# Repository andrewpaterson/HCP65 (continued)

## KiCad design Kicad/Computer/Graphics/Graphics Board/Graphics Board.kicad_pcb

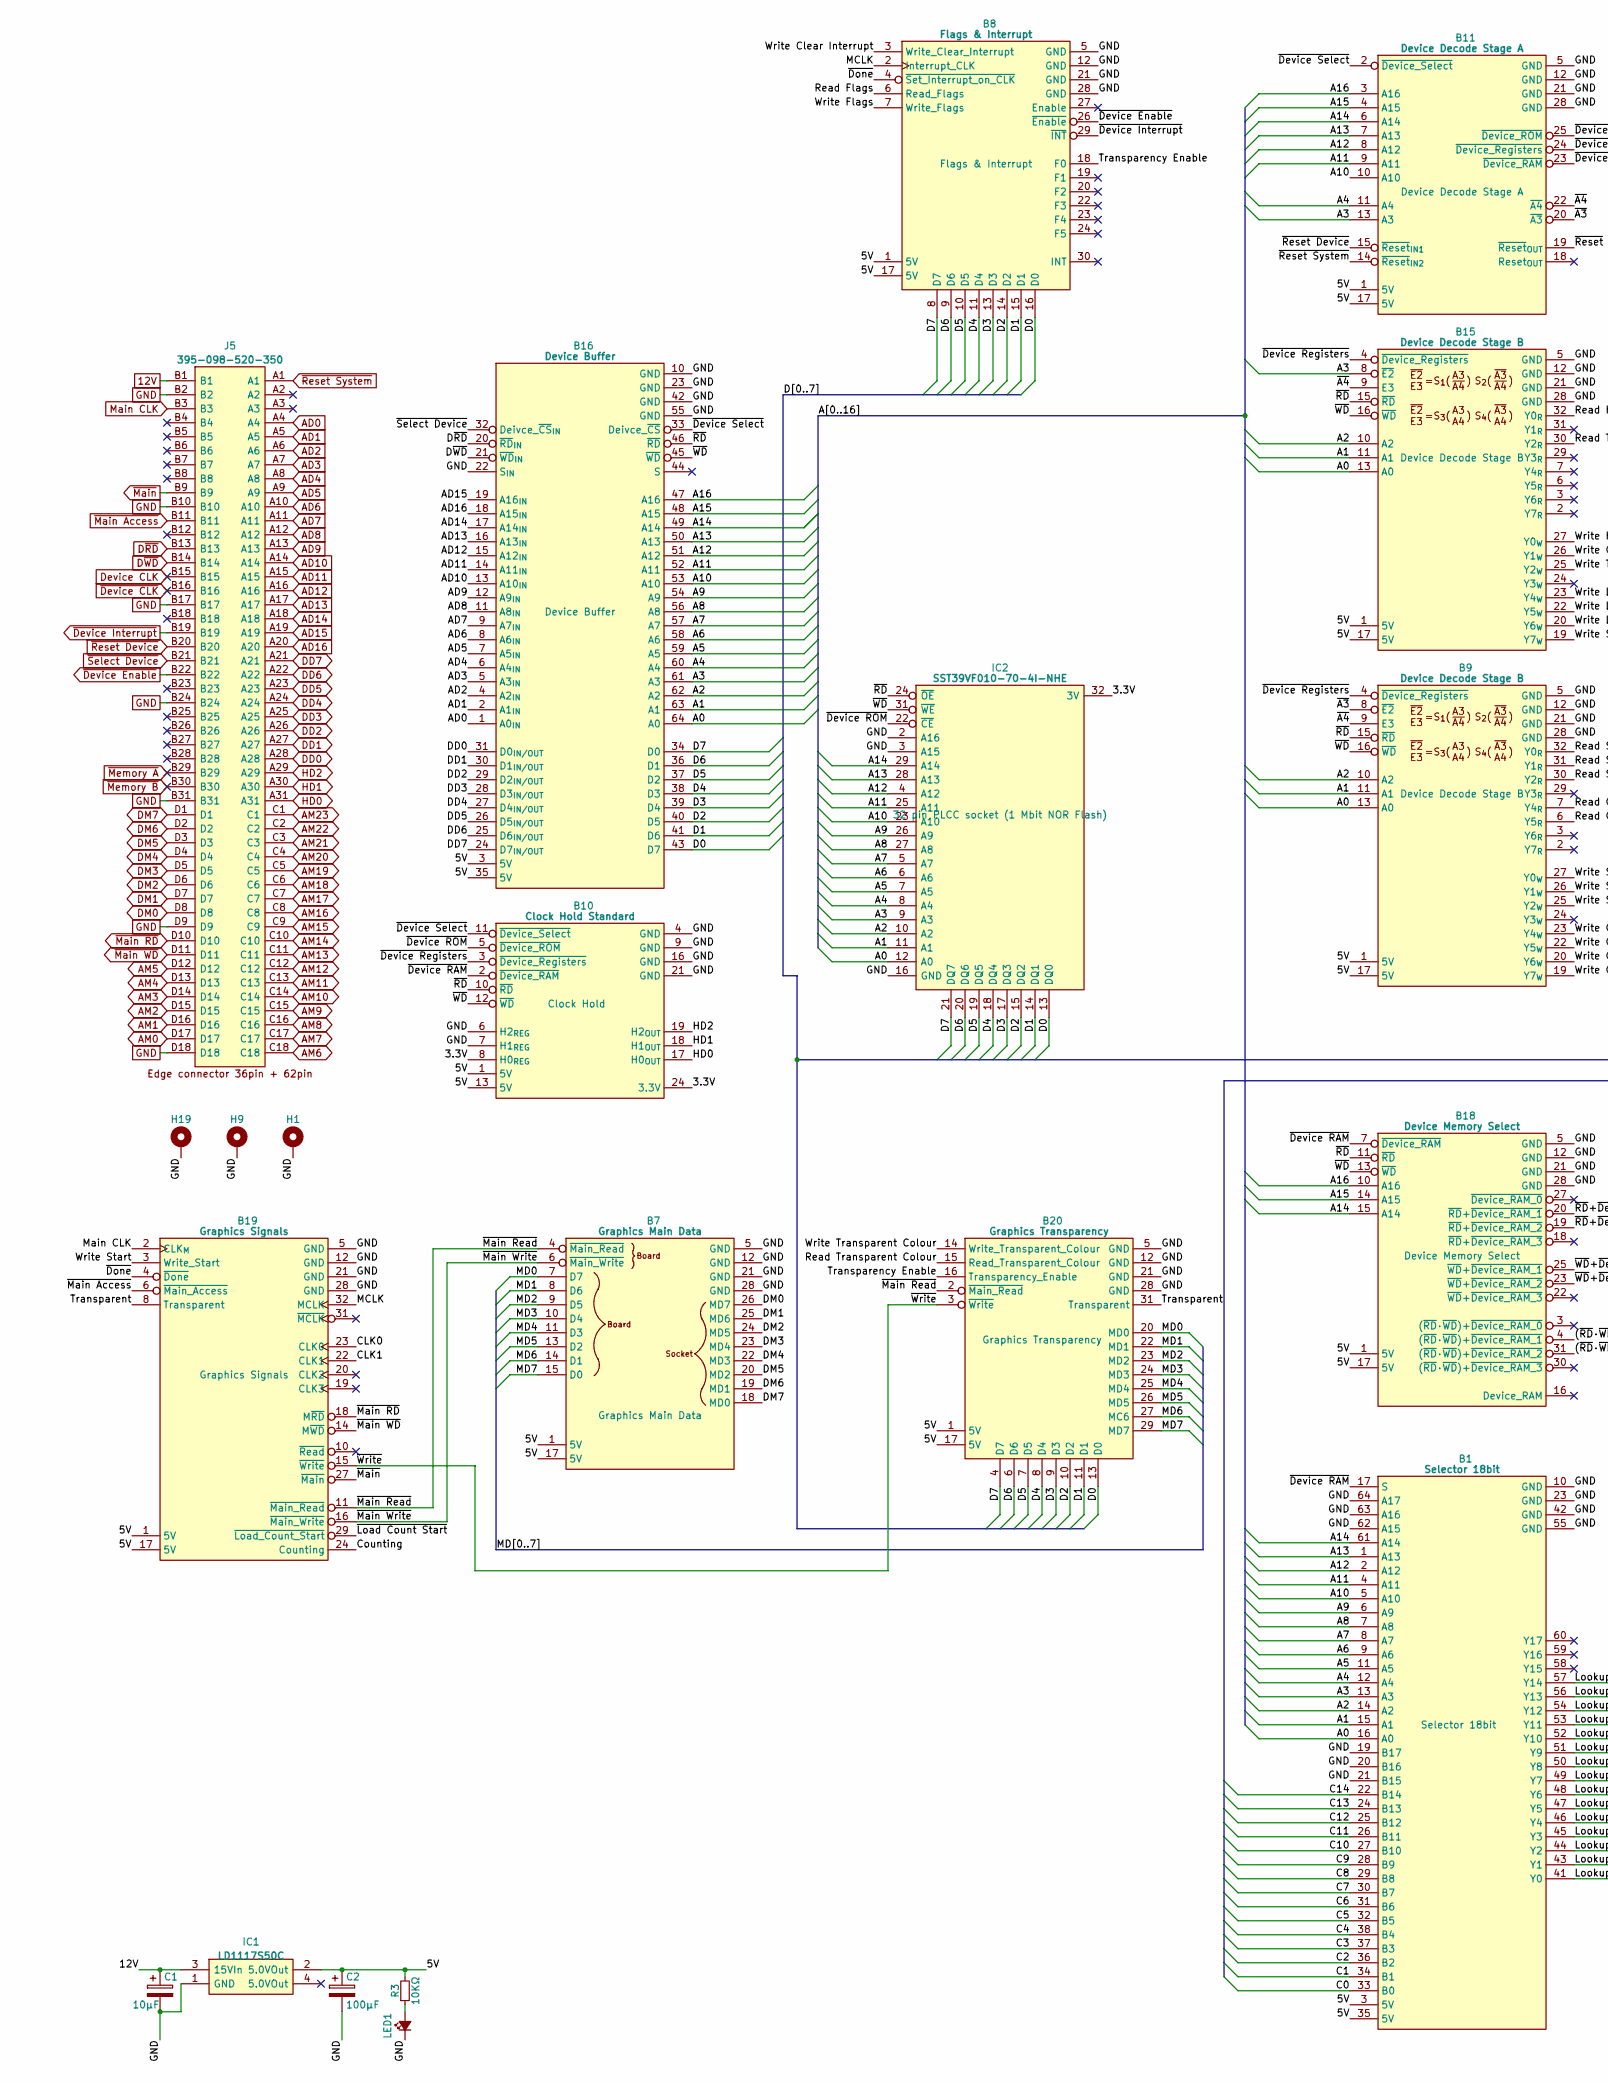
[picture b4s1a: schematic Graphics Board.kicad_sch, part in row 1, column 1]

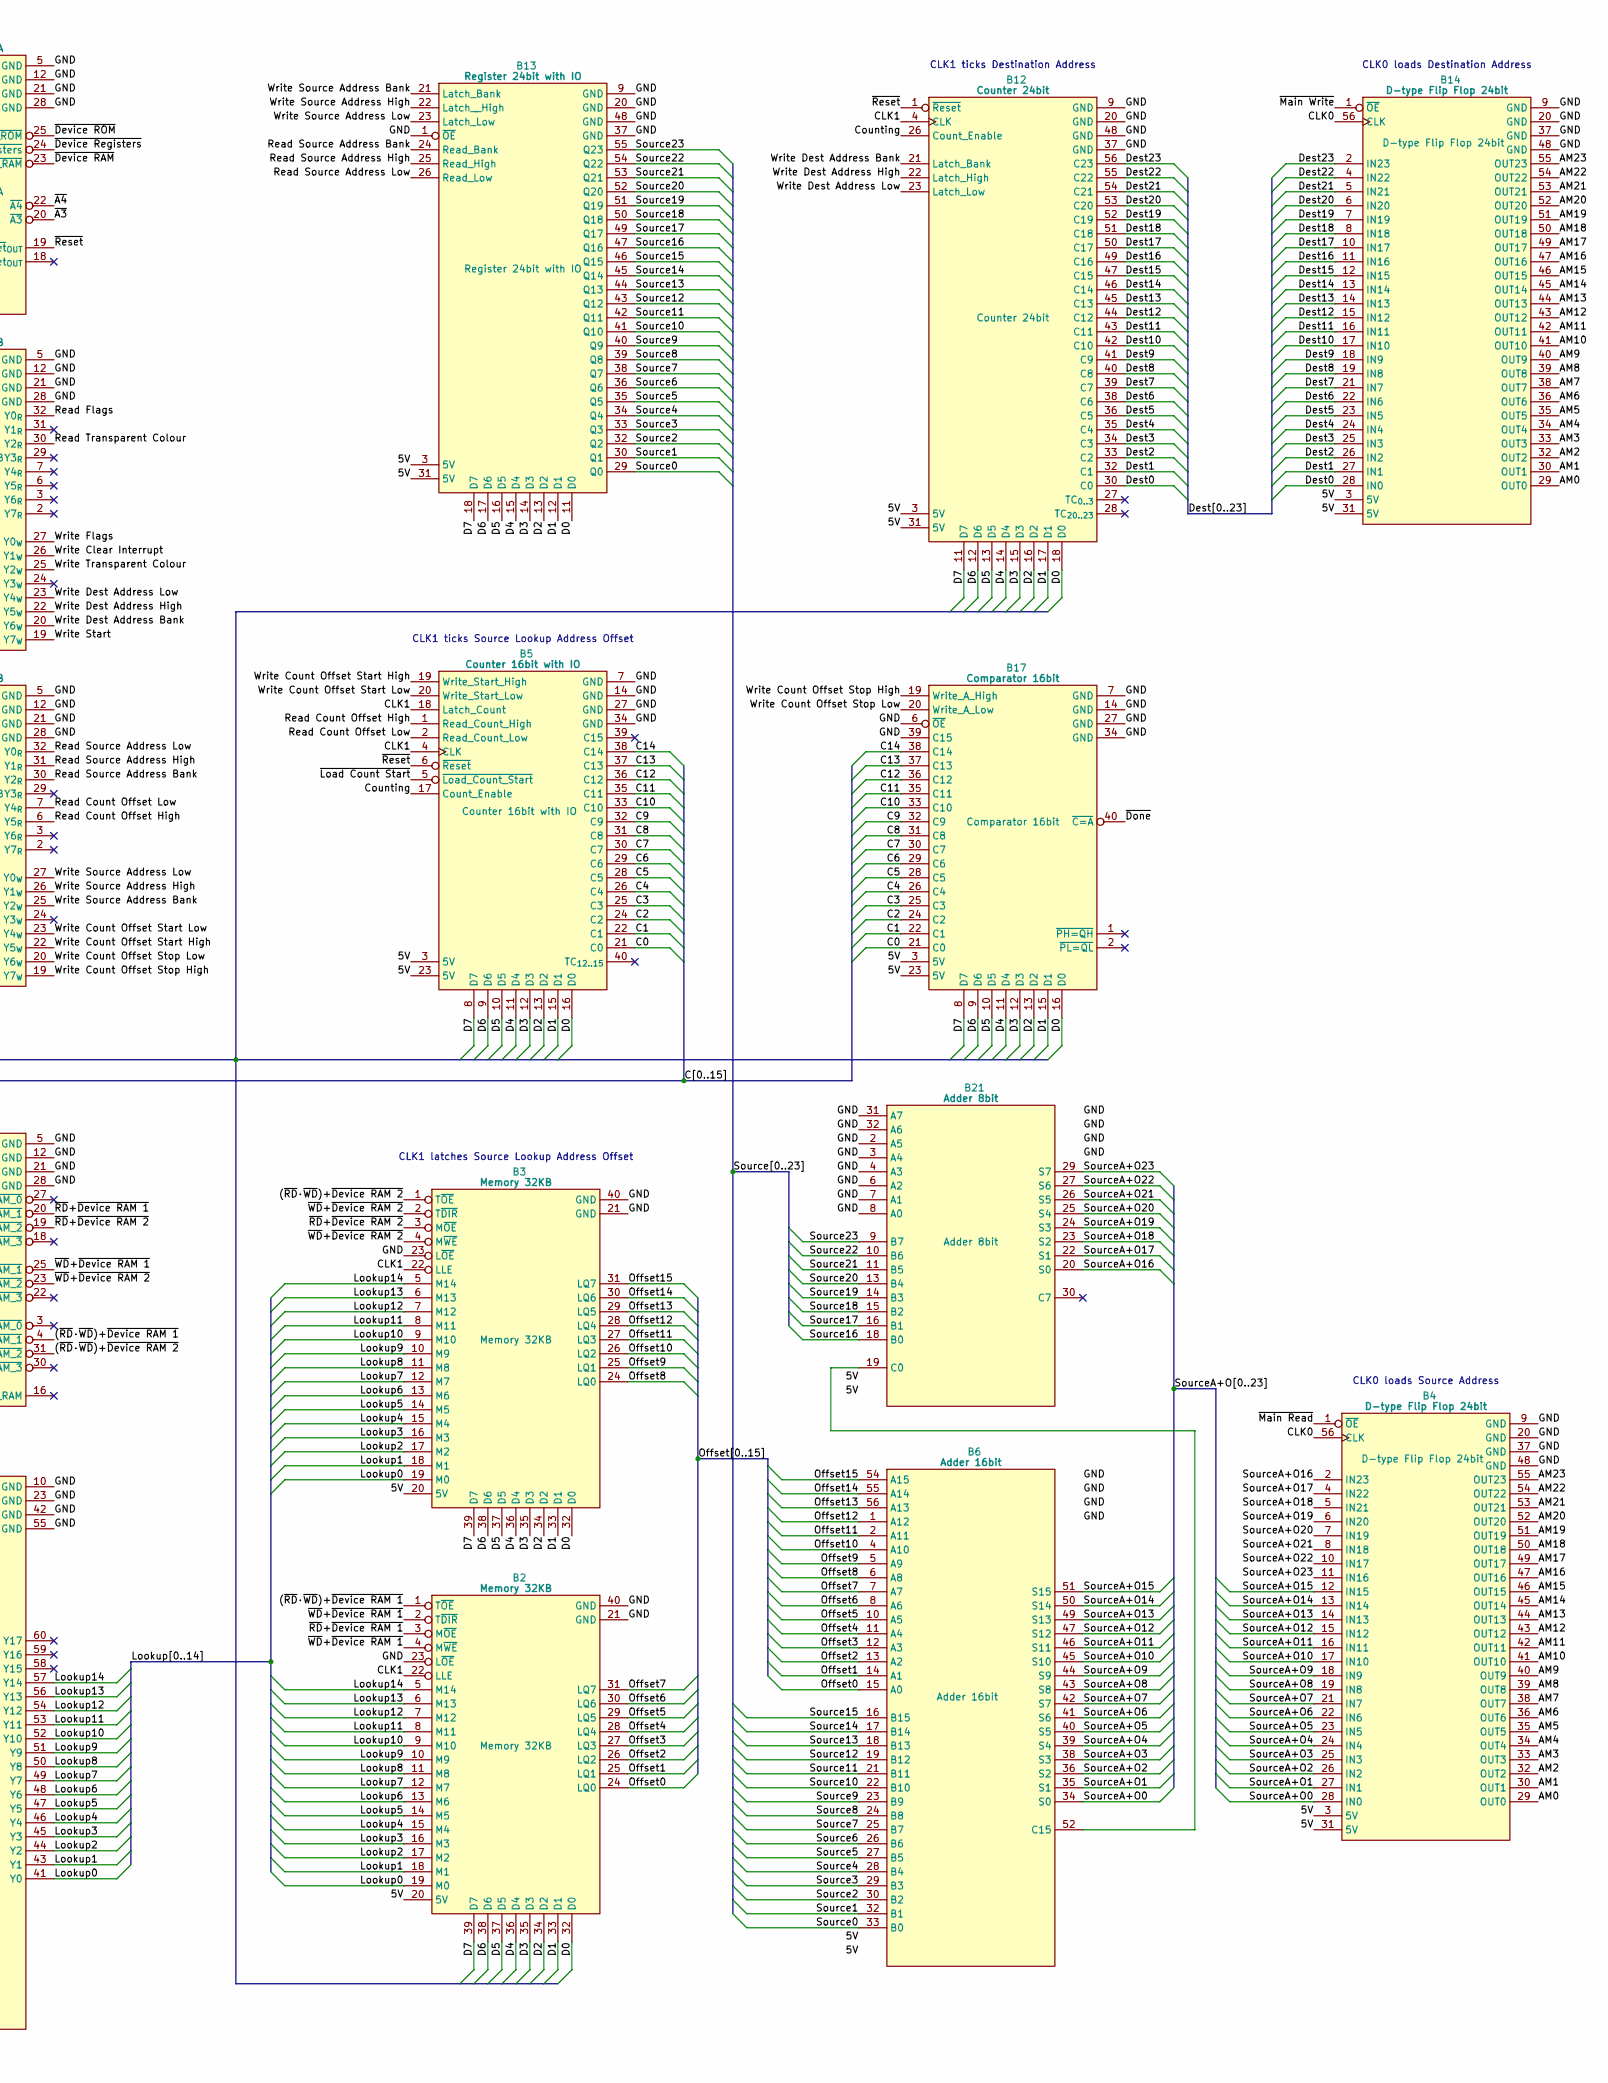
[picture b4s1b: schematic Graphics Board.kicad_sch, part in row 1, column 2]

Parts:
B1: Selector 18bit; HCP65_Selector_18bit
B2, B3: Memory 32KB; HCP65_Memory_32KB_With_Latch
B4, B14: D-type Flip Flop 24bit; HCP65_D_Flip_Flop_24bit
B5: Counter 16bit with IO; HCP65_Counter_16bit_DIO
B6: Adder 16bit; HCP65_Adder_16bit
B7: Graphics Main Data; HCP65_Graphics_Main_Data
B8: Flags & Interrupt; HCP65_Flags_Interrupt
B9, B15: Device Decode Stage B; HCP65_Device_Decode_Stage_B
B10: Clock Hold Standard; HCP65_Clock_Hold_Standard
B11: Device Decode Stage A; HCP65_Device_Decode_Stage_A
B12: Counter 24bit; HCP65_Counter_24bit
B13: Register 24bit with IO; HCP65_Register_24bit_DIO
B16: Device Buffer; HCP65_Device_Buffer
B17: Comparator 16bit; HCP65_Comparator_16bit
B18: Device Memory Select; HCP65_Video_Device_RAM_Select
B19: Graphics Signals; HCP65_Graphics_Signals
B20: Graphics Transparency; HCP65_Graphics_Transparency
B21: Adder 8bit; HCP65_Adder_8bit
C1: 10μF; CP_Radial_D4.0mm_P2.00mm
C2: 100μF; CP_Radial_D4.0mm_P2.00mm
H1, H9, H19: MountingHole_Pad; HCP65_MountingHole_M3_
IC1: LD1117S50C; LD1117S33C; Manufacturer_Part_Number LD1117S50C
IC2: SST39VF010-70-4I-NHE; 5408803224008; Manufacturer_Part_Number SST39VF010-70-4I-NHE
J5: 395-098-520-350; 98pin Edge Connector; Manufacturer_Part_Number 395-098-520-350; Mouser Part Number 587-395-098-520-350
LED1: LED; LED_D5.0mm
R3: 10KΩ; R_0805

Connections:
12V: C1.1, IC1.3 (15VIn), J5.B1
/3.3V: B10.8 (H0_{REG}), B10.24 (3.3V), IC2.32 (3V)
/5V: B1.3 (5V), B1.35 (5V), B2.20 (5V), B3.20 (5V), B4.3 (5V), B4.31 (5V), B5.3 (5V), B5.23 (5V), B6.3 (5V), B6.31 (5V), B7.1 (5V), B7.17 (5V), B8.1 (5V), B8.17 (5V), B9.1 (5V), B9.17 (5V), B10.1 (5V), B10.13 (5V), B11.1 (5V), B11.17 (5V), B12.3 (5V), B12.31 (5V), B13.3 (5V), B13.31 (5V), B14.3 (5V), B14.31 (5V), B15.1 (5V), B15.17 (5V), B16.3 (5V), B16.35 (5V), B17.3 (5V), B17.23 (5V), B18.1 (5V), B18.17 (5V), B19.1 (5V), B19.17 (5V), B20.1 (5V), B20.17 (5V), B21.1 (5V), B21.17 (5V), C2.1, IC1.2 (5.0VOut), R3.2
/(~RD·~WD)+~Device RAM 1: B2.1 (T~OE), B18.4 ((~RD·~WD)+~Device_RAM_1)
/(~RD·~WD)+~Device RAM 2: B3.1 (T~OE), B18.31 ((~RD·~WD)+~Device_RAM_2)
/A0: B1.16 (A0), B9.13 (A0), B15.13 (A0), B16.64 (A0), IC2.12 (A0)
/A1: B1.15 (A1), B9.11 (A1), B15.11 (A1), B16.63 (A1), IC2.11 (A1)
/A2: B1.14 (A2), B9.10 (A2), B15.10 (A2), B16.62 (A2), IC2.10 (A2)
/A3: B1.13 (A3), B11.13 (A3), B15.8 (~E2), B16.61 (A3), IC2.9 (A3)
/A4: B1.12 (A4), B11.11 (A4), B16.60 (A4), IC2.8 (A4)
/A5: B1.11 (A5), B16.59 (A5), IC2.7 (A5)
/A6: B1.9 (A6), B16.58 (A6), IC2.6 (A6)
/A7: B1.8 (A7), B16.57 (A7), IC2.5 (A7)
/A8: B1.7 (A8), B16.56 (A8), IC2.27 (A8)
/A9: B1.6 (A9), B16.54 (A9), IC2.26 (A9)
/A10: B1.5 (A10), B11.10 (A10), B16.53 (A10), IC2.23 (A10)
/A11: B1.4 (A11), B11.9 (A11), B16.52 (A11), IC2.25 (A11)
/A12: B1.2 (A12), B11.8 (A12), B16.51 (A12), IC2.4 (A12)
/A13: B1.1 (A13), B11.7 (A13), B16.50 (A13), IC2.28 (A13)
/A14: B1.61 (A14), B11.6 (A14), B16.49 (A14), B18.15 (A14), IC2.29 (A14)
/A15: B11.4 (A15), B16.48 (A15), B18.14 (A15)
/A16: B11.3 (A16), B16.47 (A16), B18.10 (A16)
/C0: B1.33 (B0), B5.21 (C0), B17.21 (C0)
/C1: B1.34 (B1), B5.22 (C1), B17.22 (C1)
/C2: B1.36 (B2), B5.24 (C2), B17.24 (C2)
/C3: B1.37 (B3), B5.25 (C3), B17.25 (C3)
/C4: B1.38 (B4), B5.26 (C4), B17.26 (C4)
/C5: B1.32 (B5), B5.28 (C5), B17.28 (C5)
/C6: B1.31 (B6), B5.29 (C6), B17.29 (C6)
/C7: B1.30 (B7), B5.30 (C7), B17.30 (C7)
/C8: B1.29 (B8), B5.31 (C8), B17.31 (C8)
/C9: B1.28 (B9), B5.32 (C9), B17.32 (C9)
/C10: B1.27 (B10), B5.33 (C10), B17.33 (C10)
/C11: B1.26 (B11), B5.35 (C11), B17.35 (C11)
/C12: B1.25 (B12), B5.36 (C12), B17.36 (C12)
/C13: B1.24 (B13), B5.37 (C13), B17.37 (C13)
/C14: B1.22 (B14), B5.38 (C14), B17.38 (C14)
/CLK0: B4.56 (CLK), B14.56 (CLK), B19.23 (CLK0)
/CLK1: B2.22 (LLE), B3.22 (LLE), B5.4 (CLK), B5.18 (Latch_Count), B12.4 (CLK), B19.22 (CLK1)
/Counting: B5.17 (Count_Enable), B12.26 (Count_Enable), B19.24 (Counting)
/D0: B2.32 (D0), B3.32 (D0), B5.16 (D0), B8.16 (D0), B12.18 (D0), B13.11 (D0), B16.43 (D7), B17.16 (D0), B20.13 (D0), IC2.13 (DQ0)
/D1: B2.33 (D1), B3.33 (D1), B5.15 (D1), B8.15 (D1), B12.17 (D1), B13.12 (D1), B16.41 (D6), B17.15 (D1), B20.11 (D1), IC2.14 (DQ1)
/D2: B2.34 (D2), B3.34 (D2), B5.13 (D2), B8.14 (D2), B12.16 (D2), B13.13 (D2), B16.40 (D5), B17.13 (D2), B20.10 (D2), IC2.15 (DQ2)
/D3: B2.35 (D3), B3.35 (D3), B5.12 (D3), B8.13 (D3), B12.15 (D3), B13.14 (D3), B16.39 (D4), B17.12 (D3), B20.9 (D3), IC2.17 (DQ3)
/D4: B2.36 (D4), B3.36 (D4), B5.11 (D4), B8.11 (D4), B12.14 (D4), B13.15 (D4), B16.38 (D3), B17.11 (D4), B20.8 (D4), IC2.18 (DQ4)
/D5: B2.37 (D5), B3.37 (D5), B5.10 (D5), B8.10 (D5), B12.13 (D5), B13.16 (D5), B16.37 (D2), B17.10 (D5), B20.7 (D5), IC2.19 (DQ5)
/D6: B2.38 (D6), B3.38 (D6), B5.9 (D6), B8.9 (D6), B12.12 (D6), B13.17 (D6), B16.36 (D1), B17.9 (D6), B20.6 (D6), IC2.20 (DQ6)
/D7: B2.39 (D7), B3.39 (D7), B5.8 (D7), B8.8 (D7), B12.11 (D7), B13.18 (D7), B16.34 (D0), B17.8 (D7), B20.4 (D7), IC2.21 (DQ7)
/Dest0: B12.30 (C0), B14.28 (IN0)
/Dest1: B12.32 (C1), B14.27 (IN1)
/Dest2: B12.33 (C2), B14.26 (IN2)
/Dest3: B12.34 (C3), B14.25 (IN3)
/Dest4: B12.35 (C4), B14.24 (IN4)
/Dest5: B12.36 (C5), B14.23 (IN5)
/Dest6: B12.38 (C6), B14.22 (IN6)
/Dest7: B12.39 (C7), B14.21 (IN7)
/Dest8: B12.40 (C8), B14.19 (IN8)
/Dest9: B12.41 (C9), B14.18 (IN9)
/Dest10: B12.42 (C10), B14.17 (IN10)
/Dest11: B12.43 (C11), B14.16 (IN11)
/Dest12: B12.44 (C12), B14.15 (IN12)
/Dest13: B12.45 (C13), B14.14 (IN13)
/Dest14: B12.46 (C14), B14.13 (IN14)
/Dest15: B12.47 (C15), B14.12 (IN15)
/Dest16: B12.49 (C16), B14.11 (IN16)
/Dest17: B12.50 (C17), B14.10 (IN17)
/Dest18: B12.51 (C18), B14.8 (IN18)
/Dest19: B12.52 (C19), B14.7 (IN19)
/Dest20: B12.53 (C20), B14.6 (IN20)
/Dest21: B12.54 (C21), B14.5 (IN21)
/Dest22: B12.55 (C22), B14.4 (IN22)
/Dest23: B12.56 (C23), B14.2 (IN23)
/Lookup0: B1.41 (Y0), B2.19 (M0), B3.19 (M0)
/Lookup1: B1.43 (Y1), B2.18 (M1), B3.18 (M1)
/Lookup2: B1.44 (Y2), B2.17 (M2), B3.17 (M2)
/Lookup3: B1.45 (Y3), B2.16 (M3), B3.16 (M3)
/Lookup4: B1.46 (Y4), B2.15 (M4), B3.15 (M4)
/Lookup5: B1.47 (Y5), B2.14 (M5), B3.14 (M5)
/Lookup6: B1.48 (Y6), B2.13 (M6), B3.13 (M6)
/Lookup7: B1.49 (Y7), B2.12 (M7), B3.12 (M7)
/Lookup8: B1.50 (Y8), B2.11 (M8), B3.11 (M8)
/Lookup9: B1.51 (Y9), B2.10 (M9), B3.10 (M9)
/Lookup10: B1.52 (Y10), B2.9 (M10), B3.9 (M10)
/Lookup11: B1.53 (Y11), B2.8 (M11), B3.8 (M11)
/Lookup12: B1.54 (Y12), B2.7 (M12), B3.7 (M12)
/Lookup13: B1.56 (Y13), B2.6 (M13), B3.6 (M13)
/Lookup14: B1.57 (Y14), B2.5 (M14), B3.5 (M14)
/MCLK: B8.2 (Interrupt_CLK), B19.32 (MCLK)
/MD0: B7.7 (D7), B20.20 (MD0)
/MD1: B7.8 (D6), B20.22 (MD1)
/MD2: B7.9 (D5), B20.23 (MD2)
/MD3: B7.10 (D4), B20.24 (MD3)
/MD4: B7.11 (D3), B20.25 (MD4)
/MD5: B7.13 (D2), B20.26 (MD5)
/MD6: B7.14 (D1), B20.27 (MC6)
/MD7: B7.15 (D0), B20.29 (MD7)
/Offset0: B2.24 (LQ0), B6.15 (A0)
/Offset1: B2.25 (LQ1), B6.14 (A1)
/Offset2: B2.26 (LQ2), B6.13 (A2)
/Offset3: B2.27 (LQ3), B6.12 (A3)
/Offset4: B2.28 (LQ4), B6.11 (A4)
/Offset5: B2.29 (LQ5), B6.10 (A5)
/Offset6: B2.30 (LQ6), B6.8 (A6)
/Offset7: B2.31 (LQ7), B6.7 (A7)
/Offset8: B3.24 (LQ0), B6.6 (A8)
/Offset9: B3.25 (LQ1), B6.5 (A9)
/Offset10: B3.26 (LQ2), B6.4 (A10)
/Offset11: B3.27 (LQ3), B6.2 (A11)
/Offset12: B3.28 (LQ4), B6.1 (A12)
/Offset13: B3.29 (LQ5), B6.56 (A13)
/Offset14: B3.30 (LQ6), B6.55 (A14)
/Offset15: B3.31 (LQ7), B6.54 (A15)
/Read Count Offset High: B5.1 (Read_Count_High), B9.6 (Y5_{R})
/Read Count Offset Low: B5.2 (Read_Count_Low), B9.7 (Y4_{R})
/Read Flags: B8.6 (Read_Flags), B15.32 (Y0_{R})
/Read Source Address Bank: B9.30 (Y2_{R}), B13.24 (Read_Bank)
/Read Source Address High: B9.31 (Y1_{R}), B13.25 (Read_High)
/Read Source Address Low: B9.32 (Y0_{R}), B13.26 (Read_Low)
/Read Transparent Colour: B15.30 (Y2_{R}), B20.15 (Read_Transparent_Colour)
/Source0: B6.33 (B0), B13.29 (Q0)
/Source1: B6.32 (B1), B13.30 (Q1)
/Source2: B6.30 (B2), B13.32 (Q2)
/Source3: B6.29 (B3), B13.33 (Q3)
/Source4: B6.28 (B4), B13.34 (Q4)
/Source5: B6.27 (B5), B13.35 (Q5)
/Source6: B6.26 (B6), B13.36 (Q6)
/Source7: B6.25 (B7), B13.38 (Q7)
/Source8: B6.24 (B8), B13.39 (Q8)
/Source9: B6.23 (B9), B13.40 (Q9)
/Source10: B6.22 (B10), B13.41 (Q10)
/Source11: B6.21 (B11), B13.42 (Q11)
/Source12: B6.19 (B12), B13.43 (Q12)
/Source13: B6.18 (B13), B13.44 (Q13)
/Source14: B6.17 (B14), B13.45 (Q14)
/Source15: B6.16 (B15), B13.46 (Q15)
/Source16: B13.47 (Q16), B21.18 (B0)
/Source17: B13.49 (Q17), B21.16 (B1)
/Source18: B13.50 (Q18), B21.15 (B2)
/Source19: B13.51 (Q19), B21.14 (B3)
/Source20: B13.52 (Q20), B21.13 (B4)
/Source21: B13.53 (Q21), B21.11 (B5)
/Source22: B13.54 (Q22), B21.10 (B6)
/Source23: B13.55 (Q23), B21.9 (B7)
/SourceA+O0: B4.28 (IN0), B6.34 (S0)
/SourceA+O1: B4.27 (IN1), B6.35 (S1)
/SourceA+O2: B4.26 (IN2), B6.36 (S2)
/SourceA+O3: B4.25 (IN3), B6.38 (S3)
/SourceA+O4: B4.24 (IN4), B6.39 (S4)
/SourceA+O5: B4.23 (IN5), B6.40 (S5)
/SourceA+O6: B4.22 (IN6), B6.41 (S6)
/SourceA+O7: B4.21 (IN7), B6.42 (S7)
/SourceA+O8: B4.19 (IN8), B6.43 (S8)
/SourceA+O9: B4.18 (IN9), B6.44 (S9)
/SourceA+O10: B4.17 (IN10), B6.45 (S10)
/SourceA+O11: B4.16 (IN11), B6.46 (S11)
/SourceA+O12: B4.15 (IN12), B6.47 (S12)
/SourceA+O13: B4.14 (IN13), B6.49 (S13)
/SourceA+O14: B4.13 (IN14), B6.50 (S14)
/SourceA+O15: B4.12 (IN15), B6.51 (S15)
/SourceA+O16: B4.2 (IN23), B21.20 (S0)
/SourceA+O17: B4.4 (IN22), B21.22 (S1)
/SourceA+O18: B4.5 (IN21), B21.23 (S2)
/SourceA+O19: B4.6 (IN20), B21.24 (S3)
/SourceA+O20: B4.7 (IN19), B21.25 (S4)
/SourceA+O21: B4.8 (IN18), B21.26 (S5)
/SourceA+O22: B4.10 (IN17), B21.27 (S6)
/SourceA+O23: B4.11 (IN16), B21.29 (S7)
/Transparency Enable: B8.18 (F0), B20.16 (Transparency_Enable)
/Transparent: B19.8 (Transparent), B20.31 (Transparent)
/Write Clear Interrupt: B8.3 (Write_Clear_Interrupt), B15.26 (Y1_{W})
/Write Count Offset Start High: B5.19 (Write_Start_High), B9.22 (Y5_{W})
/Write Count Offset Start Low: B5.20 (Write_Start_Low), B9.23 (Y4_{W})
/Write Count Offset Stop High: B9.19 (Y7_{W}), B17.19 (Write_A_High)
/Write Count Offset Stop Low: B9.20 (Y6_{W}), B17.20 (Write_A_Low)
/Write Dest Address Bank: B12.21 (Latch_Bank), B15.20 (Y6_{W})
/Write Dest Address High: B12.22 (Latch_High), B15.22 (Y5_{W})
/Write Dest Address Low: B12.23 (Latch_Low), B15.23 (Y4_{W})
/Write Flags: B8.7 (Write_Flags), B15.27 (Y0_{W})
/Write Source Address Bank: B9.25 (Y2_{W}), B13.21 (Latch_Bank)
/Write Source Address High: B9.26 (Y1_{W}), B13.22 (Latch__High)
/Write Source Address Low: B9.27 (Y0_{W}), B13.23 (Latch_Low)
/Write Start: B15.19 (Y7_{W}), B19.3 (Write_Start)
/Write Transparent Colour: B15.25 (Y2_{W}), B20.14 (Write_Transparent_Colour)
/~A3: B9.8 (~E2), B11.20 (~A3)
/~A4: B9.9 (E3), B11.22 (~A4), B15.9 (E3)
/~Device RAM: B1.17 (S), B10.2 (~Device_RAM), B11.23 (~Device_RAM), B18.7 (~Device_RAM)
/~Device ROM: B10.5 (~Device_ROM), B11.25 (~Device_ROM), IC2.22 (~CE)
/~Device Registers: B9.4 (~Device_Registers), B10.3 (~Device_Registers), B11.24 (~Device_Registers), B15.4 (~Device_Registers)
/~Device Select: B10.11 (~Device_Select), B11.2 (~Device_Select), B16.33 (Deivce_~CS)
/~Done: B8.4 (~Set_Interrupt_on_CLK), B17.40 (~C=A), B19.4 (~Done)
/~Load Count Start: B5.5 (~Load_Count_Start), B19.29 (~Load_Count_Start)
/~Main Read: B4.1 (~OE), B7.4 (~Main_Read), B19.11 (~Main_Read), B20.2 (~Main_Read)
/~Main Write: B7.6 (~Main_Write), B14.1 (~OE), B19.16 (~Main_Write)
/~RD: B9.15 (~RD), B10.10 (~RD), B15.15 (~RD), B16.46 (~RD), B18.11 (~RD), IC2.24 (~OE)
/~RD+~Device RAM 1: B2.3 (M~OE), B18.20 (~RD+~Device_RAM_1)
/~RD+~Device RAM 2: B3.3 (M~OE), B18.19 (~RD+~Device_RAM_2)
/~Reset: B5.6 (~Reset), B11.19 (~Reset_{OUT}), B12.1 (~Reset)
/~WD: B9.16 (~WD), B10.12 (~WD), B15.16 (~WD), B16.45 (~WD), B18.13 (~WD), IC2.31 (~WE)
/~WD+~Device RAM 1: B2.2 (T~DIR), B2.4 (M~WE), B18.25 (~WD+~Device_RAM_1)
/~WD+~Device RAM 2: B3.2 (T~DIR), B3.4 (M~WE), B18.23 (~WD+~Device_RAM_2)
/~Write: B19.15 (~Write), B20.3 (~Write)
AD0: B16.1 (A0_{IN}), J5.A4
AD1: B16.2 (A1_{IN}), J5.A5
AD2: B16.4 (A2_{IN}), J5.A6
AD3: B16.5 (A3_{IN}), J5.A7
AD4: B16.6 (A4_{IN}), J5.A8
AD5: B16.7 (A5_{IN}), J5.A9
AD6: B16.8 (A6_{IN}), J5.A10
AD7: B16.9 (A7_{IN}), J5.A11
AD8: B16.11 (A8_{IN}), J5.A12
AD9: B16.12 (A9_{IN}), J5.A13
AD10: B16.13 (A10_{IN}), J5.A14
AD11: B16.14 (A11_{IN}), J5.A15
AD12: B16.15 (A12_{IN}), J5.A16
AD13: B16.16 (A13_{IN}), J5.A17
AD14: B16.17 (A14_{IN}), J5.A18
AD15: B16.19 (A16_{IN}), J5.A19
AD16: B16.18 (A15_{IN}), J5.A20
AM0: B4.29 (OUT0), B14.29 (OUT0), J5.D17
AM1: B4.30 (OUT1), B14.30 (OUT1), J5.D16
AM2: B4.32 (OUT2), B14.32 (OUT2), J5.D15
AM3: B4.33 (OUT3), B14.33 (OUT3), J5.D14
AM4: B4.34 (OUT4), B14.34 (OUT4), J5.D13
AM5: B4.35 (OUT5), B14.35 (OUT5), J5.D12
AM6: B4.36 (OUT6), B14.36 (OUT6), J5.C18
AM7: B4.38 (OUT7), B14.38 (OUT7), J5.C17
AM8: B4.39 (OUT8), B14.39 (OUT8), J5.C16
AM9: B4.40 (OUT9), B14.40 (OUT9), J5.C15
AM10: B4.41 (OUT10), B14.41 (OUT10), J5.C14
AM11: B4.42 (OUT11), B14.42 (OUT11), J5.C13
AM12: B4.43 (OUT12), B14.43 (OUT12), J5.C12
AM13: B4.44 (OUT13), B14.44 (OUT13), J5.C11
AM14: B4.45 (OUT14), B14.45 (OUT14), J5.C10
AM15: B4.46 (OUT15), B14.46 (OUT15), J5.C9
AM16: B4.47 (OUT16), B14.47 (OUT16), J5.C8
AM17: B4.49 (OUT17), B14.49 (OUT17), J5.C7
AM18: B4.50 (OUT18), B14.50 (OUT18), J5.C6
AM19: B4.51 (OUT19), B14.51 (OUT19), J5.C5
AM20: B4.52 (OUT20), B14.52 (OUT20), J5.C4
AM21: B4.53 (OUT21), B14.53 (OUT21), J5.C3
AM22: B4.54 (OUT22), B14.54 (OUT22), J5.C2
AM23: B4.55 (OUT23), B14.55 (OUT23), J5.C1
DD0: B16.31 (D0_{IN/OUT}), J5.A28
DD1: B16.30 (D1_{IN/OUT}), J5.A27
DD2: B16.29 (D2_{IN/OUT}), J5.A26
DD3: B16.28 (D3_{IN/OUT}), J5.A25
DD4: B16.27 (D4_{IN/OUT}), J5.A24
DD5: B16.26 (D5_{IN/OUT}), J5.A23
DD6: B16.25 (D6_{IN/OUT}), J5.A22
DD7: B16.24 (D7_{IN/OUT}), J5.A21
DM0: B7.26 (MD7), J5.D8
DM1: B7.25 (MD6), J5.D7
DM2: B7.24 (MD5), J5.D6
DM3: B7.23 (MD4), J5.D5
DM4: B7.22 (MD3), J5.D4
DM5: B7.20 (MD2), J5.D3
DM6: B7.19 (MD1), J5.D2
DM7: B7.18 (MD0), J5.D1
Device CLK: J5.B15
D~RD: B16.20 (~RD_{IN}), J5.B13
D~WD: B16.21 (~WD_{IN}), J5.B14
GND: B1.10 (GND), B1.19 (B17), B1.20 (B16), B1.21 (B15), B1.23 (GND), B1.42 (GND), B1.55 (GND), B1.62 (A15), B1.63 (A16), B1.64 (A17), B2.21 (GND), B2.23 (L~OE), B2.40 (GND), B3.21 (GND), B3.23 (L~OE), B3.40 (GND), B4.9 (GND), B4.20 (GND), B4.37 (GND), B4.48 (GND), B5.7 (GND), B5.14 (GND), B5.27 (GND), B5.34 (GND), B6.9 (GND), B6.20 (GND), B6.37 (GND), B6.48 (GND), B7.5 (GND), B7.12 (GND), B7.21 (GND), B7.28 (GND), B8.5 (GND), B8.12 (GND), B8.21 (GND), B8.28 (GND), B9.5 (GND), B9.12 (GND), B9.21 (GND), B9.28 (GND), B10.4 (GND), B10.6 (H2_{REG}), B10.7 (H1_{REG}), B10.9 (GND), B10.16 (GND), B10.21 (GND), B11.5 (GND), B11.12 (GND), B11.21 (GND), B11.28 (GND), B12.9 (GND), B12.20 (GND), B12.37 (GND), B12.48 (GND), B13.1 (~OE), B13.9 (GND), B13.20 (GND), B13.37 (GND), B13.48 (GND), B14.9 (GND), B14.20 (GND), B14.37 (GND), B14.48 (GND), B15.5 (GND), B15.12 (GND), B15.21 (GND), B15.28 (GND), B16.10 (GND), B16.22 (S_{IN}), B16.23 (GND), B16.42 (GND), B16.55 (GND), B17.6 (~OE), B17.7 (GND), B17.14 (GND), B17.27 (GND), B17.34 (GND), B17.39 (C15), B18.5 (GND), B18.12 (GND), B18.21 (GND), B18.28 (GND), B19.5 (GND), B19.12 (GND), B19.21 (GND), B19.28 (GND), B20.5 (GND), B20.12 (GND), B20.21 (GND), B20.28 (GND), B21.2 (A5), B21.3 (A4), B21.4 (A3), B21.5 (GND), B21.6 (A2), B21.7 (A1), B21.8 (A0), B21.12 (GND), B21.21 (GND), B21.28 (GND), B21.31 (A7), B21.32 (A6), C1.2, C2.2, H1.1 (GND), H9.1 (GND), H19.1 (GND), IC1.1 (GND), IC2.2 (A16), IC2.3 (A15), IC2.16 (GND), J5.B2, J5.B10, J5.B17, J5.B24, J5.B31, J5.D9, J5.D18, LED1.1 (K)
HD0: B10.17 (H0_{OUT}), J5.A31
HD1: B10.18 (H1_{OUT}), J5.A30
HD2: B10.19 (H2_{OUT}), J5.A29
Main CLK: B19.2 (CLK_{M}), J5.B3
unnamed: B6.52 (C15), B21.19 (C0)
unnamed: LED1.2 (A), R3.1
~Device CLK: J5.B16
~Device Enable: B8.26 (~Enable), J5.B22
~Device Interrupt: B8.29 (~INT), J5.B19
~Main Access: B19.6 (~Main_Access), J5.B11
~Main RD: B19.18 (M~RD), J5.D10
~Main WD: B19.14 (M~WD), J5.D11
~Main: B19.27 (~Main), J5.B9
~Memory A: J5.B29
~Memory B: J5.B30
~Reset Device: B11.15 (~Reset_{IN1}), J5.B20
~Reset System: B11.14 (~Reset_{IN2}), J5.A1
~Select Device: B16.32 (Deivce_~CS_{IN}), J5.B21

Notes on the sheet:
CLK1 ticks Source Lookup Address Offset
CLK0 loads Destination Address
CLK1 ticks Destination Address
CLK0 loads Source Address
CLK1 latches Source Lookup Address Offset

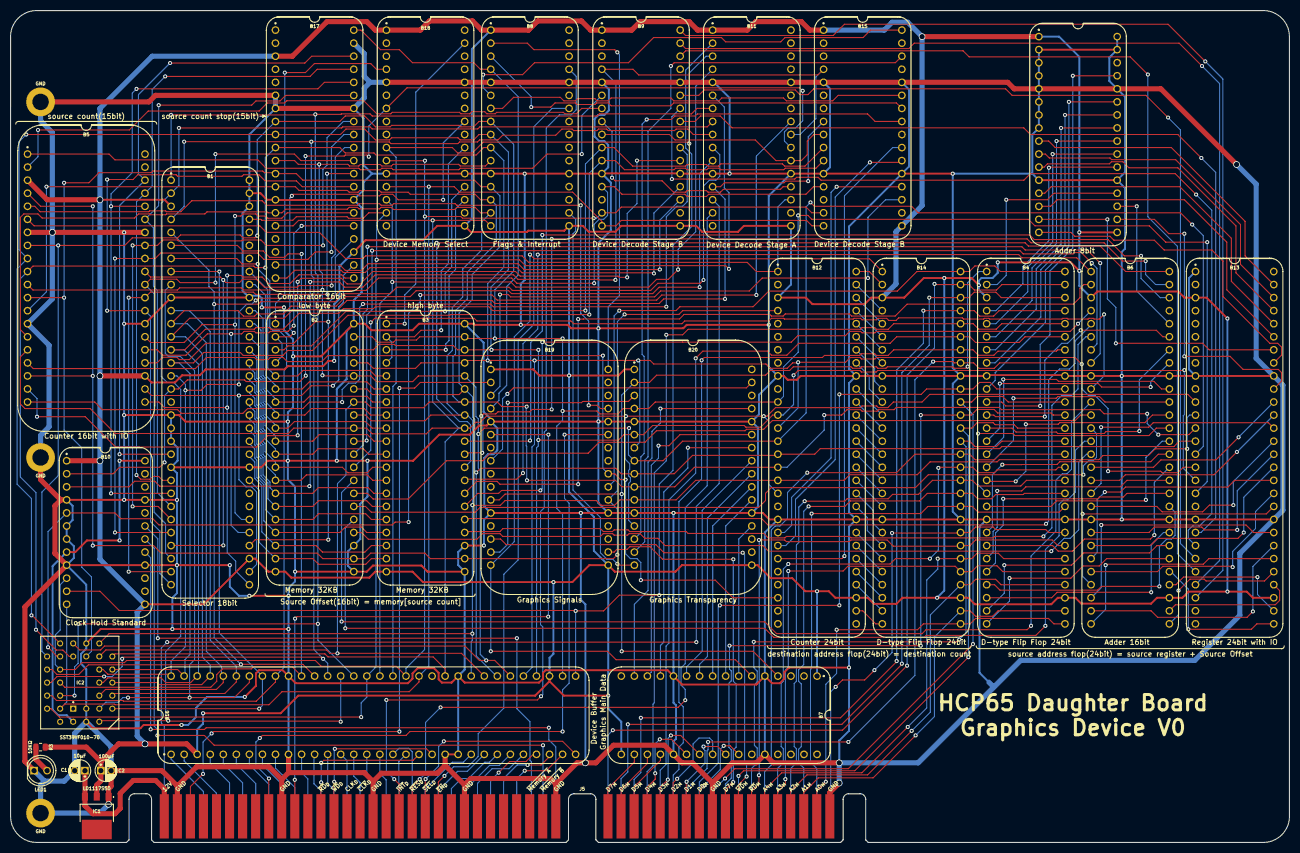
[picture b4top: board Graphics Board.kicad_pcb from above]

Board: 2 copper layers, 248.9 x 161.9 mm, 31 parts (0 on the bottom side), 276 nets.

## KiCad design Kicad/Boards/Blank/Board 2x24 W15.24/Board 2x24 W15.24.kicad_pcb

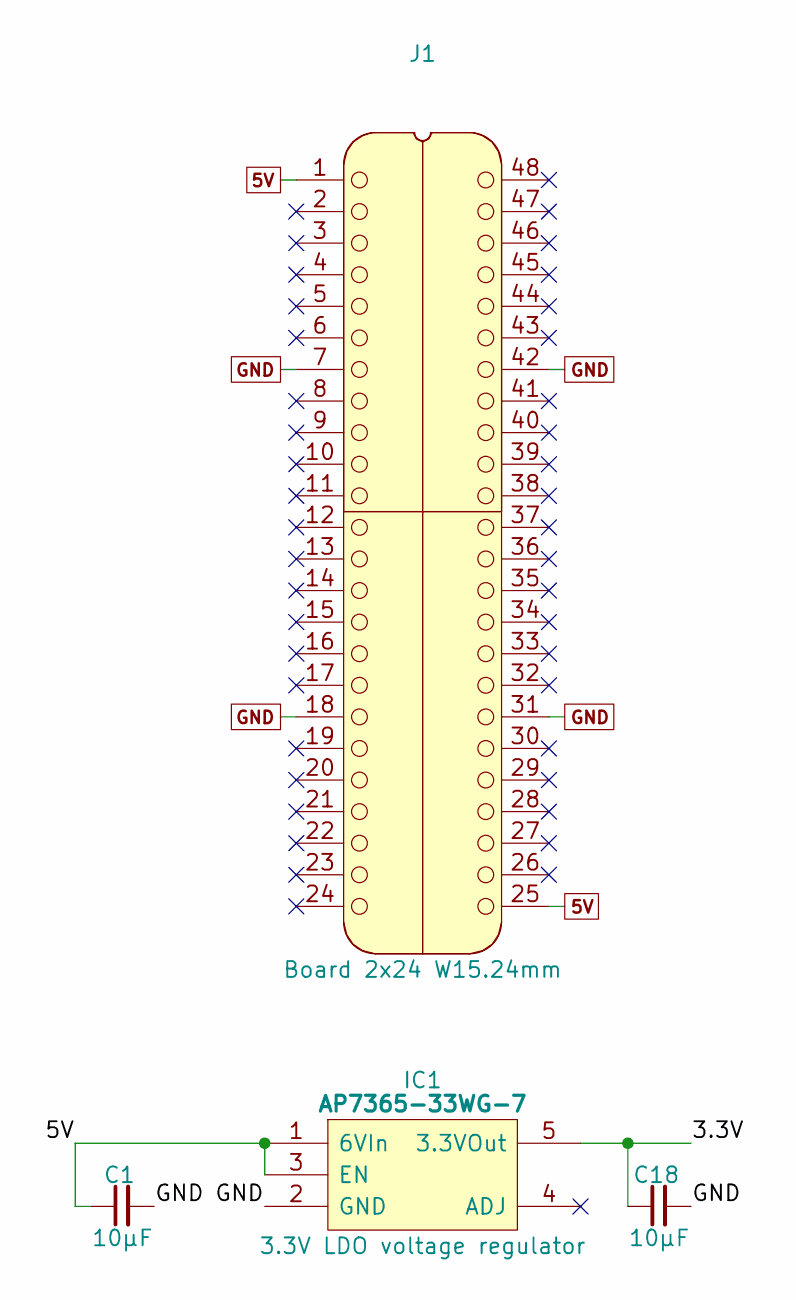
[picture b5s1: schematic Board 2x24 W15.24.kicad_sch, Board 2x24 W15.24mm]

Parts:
C1, C18: 10µF; C_0805
IC1: AP7365-33WG-7; SOT95P285X130-5N; Manufacturer_Part_Number AP7365-33WG-7; Mouser Part Number 621-AP7365-33WG-7
J1: Board 2x24 W15.24mm; DIP-48_Board_W15.24mm

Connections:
5V: C1.1, IC1.1 (6VIn), IC1.3 (EN), J1.1, J1.25
/3.3V: C18.1, IC1.5 (3.3VOut)
GND: C1.2, C18.2, IC1.2 (GND), J1.7, J1.18, J1.31, J1.42

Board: 2 copper layers, 4 parts (0 on the bottom side), 3 nets, no tracks yet.

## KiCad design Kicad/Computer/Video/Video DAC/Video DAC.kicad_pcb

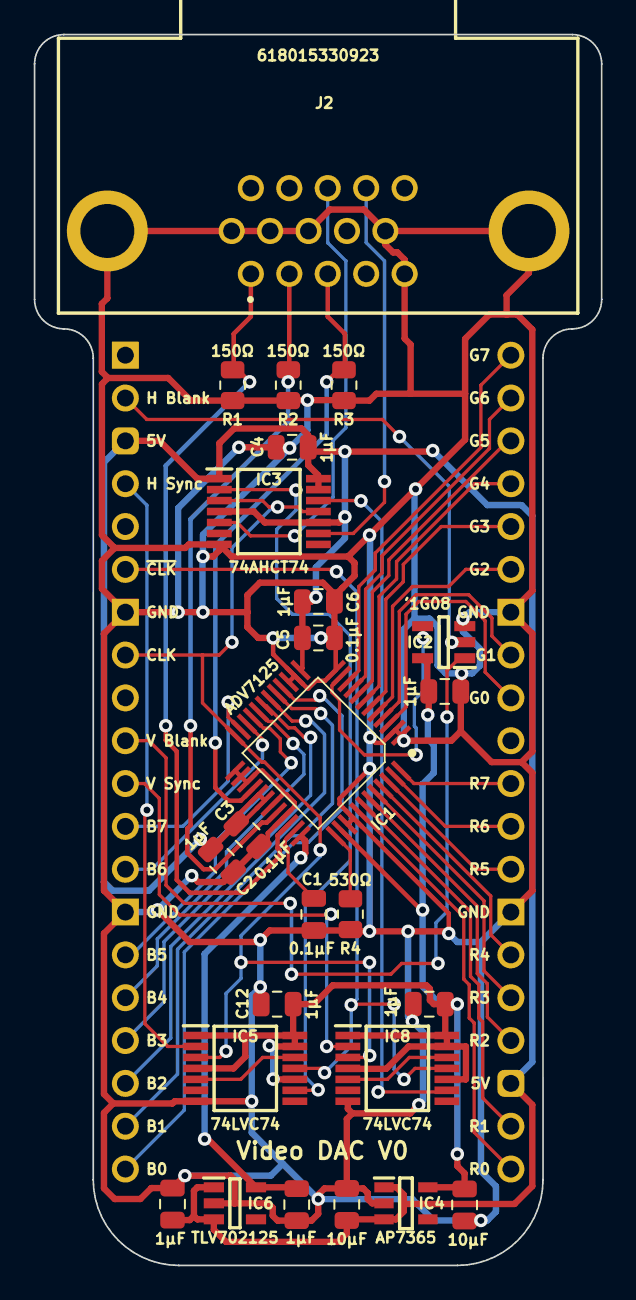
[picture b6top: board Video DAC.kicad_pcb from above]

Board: 2 copper layers, 33.6 x 73.0 mm, 26 parts (0 on the bottom side), 46 nets.

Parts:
C1, C3, C5: 0.1μF; C_0805
C2, C4, C6, C7, C12, C13: 1μF; C_0805
C8, C11: 1µF; C_0805
C9, C10: 10µF; C_0805
IC1: ADV7125KSTZ50; QFP50P900X900X160-48N
IC2: 74LVC1G08GV,125; SOT95P275X110-5N
IC3: SN74AHCT74PWR; SOP65P640X110-14N
IC4: AP7365-33WG-7; SOT95P285X130-5N
IC5, IC8: 74LVC74APW,118; SOP65P640X110-14N
IC6: TLV702125QDBVRQ1; SOT95P280X145-5N
J2: 618015330923
J3: Board 2x20 W22.86mm; DIP-40_Board_W22.86mm_Nak
R1, R2, R3: 150Ω; R_0805
R4: 530Ω; R_0805

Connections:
5V: C2.1, C3.1, C4.1, C5.1, C6.1, C8.1, C9.1, IC1.13 (5V), IC1.29 (5V), IC1.30 (5V), IC3.1 (~1RD), IC3.4 (~1SD), IC3.10 (~2SD), IC3.13 (~2RD), IC3.14 (5V), IC4.1 (6VIn), IC4.3 (EN), IC6.1 (5VIn), IC6.3 (EN), J3.3, J3.23
/1.25V: C11.1, IC1.36 (Voltage_{REF}), IC6.5 (1.25VOut)
/3.3V: C7.1, C10.1, C12.1, C13.1, IC1.38 (~PSAVE), IC2.5 (3V), IC4.5 (3.3VOut), IC5.1 (~1RD), IC5.4 (~1SD), IC5.10 (~2SD), IC5.13 (~2RD), IC5.14 (3V), IC8.1 (~1RD), IC8.4 (~1SD), IC8.10 (~2SD), IC8.13 (~2RD), IC8.14 (3V)
/Blank: IC1.11 (~BLANK), IC2.4 (Y)
/Blue _{OUT}: IC1.28 (IOB), J2.3 (BLUE), R3.1
/Green _{OUT}: IC1.32 (IOG), J2.2 (GREEN), R2.1
/Horizontal Sync _{HALF}: IC3.2 (1D), IC5.9 (2Q)
/Horizontal Sync _{OUT}: IC3.5 (1Q), J2.13 (HSYNC)
/Horizontal Sync _{~HALF}: IC5.5 (1Q), IC5.12 (2D)
/Red _{OUT}: IC1.34 (IOR), J2.1 (RED), R1.1
/Vertical Sync _{HALF}: IC3.12 (2D), IC8.9 (2Q)
/Vertical Sync _{OUT}: IC3.9 (2Q), J2.14 (VSYNC)
/Vertical Sync _{~HALF}: IC8.5 (1Q), IC8.12 (2D)
Blue0: IC1.16 (B0), J3.20
Blue1: IC1.17 (B1), J3.19
Blue2: IC1.18 (B2), J3.18
Blue3: IC1.19 (B3), J3.17
Blue4: IC1.20 (B4), J3.16
Blue5: IC1.21 (B5), J3.15
Blue6: IC1.22 (B6), J3.13
Blue7: IC1.23 (B7), J3.12
CLK: IC1.24 (CLK), IC3.3 (1CP), IC3.11 (2CP), IC5.3 (1CP), IC8.3 (1CP), J3.8
GND: C1.2, C2.2, C3.2, C4.2, C5.2, C6.2, C7.2, C8.2, C9.2, C10.2, C11.2, C12.2, C13.2, IC1.1 (GND), IC1.2 (GND), IC1.12 (~SYNC), IC1.14 (GND), IC1.15 (GND), IC1.25 (GND), IC1.26 (GND), IC1.27 (~IOB), IC1.31 (~IOG), IC1.33 (~IOR), IC1.39 (GND), IC1.40 (GND), IC2.3 (GND), IC3.7 (GND), IC4.2 (GND), IC5.7 (GND), IC6.2 (GND), IC8.7 (GND), J2.5 (GND), J2.6 (GND), J2.7 (GND), J2.8 (GND), J2.10 (GND), J2.MH1, J2.MH2, J3.7, J3.14, J3.27, J3.34, R1.2, R2.2, R3.2, R4.2
Green0: IC1.3 (G0), J3.32
Green1: IC1.4 (G1), J3.33
Green2: IC1.5 (G2), J3.35
Green3: IC1.6 (G3), J3.36
Green4: IC1.7 (G4), J3.37
Green5: IC1.8 (G5), J3.38
Green6: IC1.9 (G6), J3.39
Green7: IC1.10 (G7), J3.40
Horizontal Blank: IC2.2 (A), J3.2
Horizontal Sync: IC5.2 (1D), J3.4
unnamed: C1.1, IC1.35 (Capacitor_{COMP})
unnamed: IC1.37 (Resistor_{SET}), R4.1
Red0: IC1.41 (R0), J3.21
Red1: IC1.42 (R1), J3.22
Red2: IC1.43 (R2), J3.24
Red3: IC1.44 (R3), J3.25
Red4: IC1.45 (R4), J3.26
Red5: IC1.46 (R5), J3.28
Red6: IC1.47 (R6), J3.29
Red7: IC1.48 (R7), J3.30
Vertical Blank: IC2.1 (B), J3.10
Vertical Sync: IC8.2 (1D), J3.11
~CLK: IC5.11 (2CP), IC8.11 (2CP), J3.6

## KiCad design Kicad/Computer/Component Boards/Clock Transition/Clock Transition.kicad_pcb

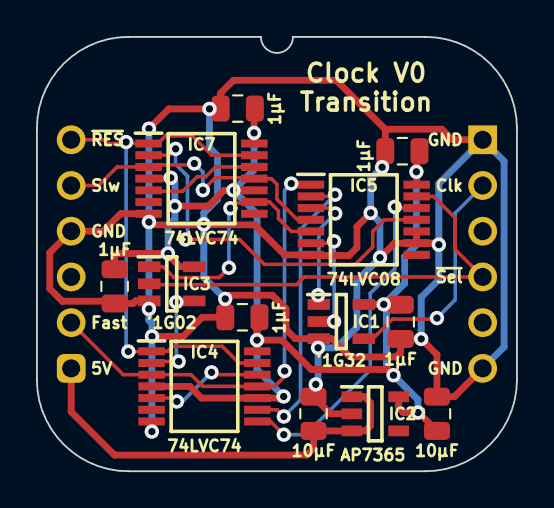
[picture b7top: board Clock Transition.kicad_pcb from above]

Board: 2 copper layers, 26.7 x 24.1 mm, 14 parts (0 on the bottom side), 17 nets.

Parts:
C1, C2, C3, C5, C6: 1μF; C_0805
C43, C44: 10μF; C_0805
IC1: 74LVC1G32GV,125; SOT95P275X110-5N
IC2: AP7365-33WG-7; SOT95P285X130-5N
IC3: 74LVC1G02GV,125; SOT95P275X110-5N
IC4, IC7: 74LVC74APW,118; SOP65P640X110-14N
IC5: 74LVC08APW,112; SOP65P640X110-14N
J1: Board 2x06 W22.86mm; DIP-12_Board_W22.86mm_Alt

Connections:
5V: C43.1, IC2.1 (6VIn), IC2.3 (EN), J1.6
/3.3V: C1.1, C2.1, C3.1, C5.1, C6.1, C44.1, IC1.5 (3V), IC2.5 (3.3VOut), IC3.5 (3V), IC4.4 (~1SD), IC4.10 (~2SD), IC4.14 (3V), IC5.14 (3V), IC7.4 (~1SD), IC7.10 (~2SD), IC7.14 (3V)
/Clock1_{Q}: IC4.9 (2Q), IC5.2 (1B)
/Clock2_{Q}: IC3.1 (B), IC5.5 (2B), IC7.9 (2Q)
/~Clock1_{Q}: IC4.8 (~2Q), IC5.12 (4A)
Clock: IC1.4 (Y), J1.11
Fast Clock: IC4.3 (1CP), IC4.11 (2CP), IC5.1 (1A), J1.5
GND: C1.2, C2.2, C3.2, C5.2, C6.2, C43.2, C44.2, IC1.3 (GND), IC2.2 (GND), IC3.3 (GND), IC4.7 (GND), IC5.7 (GND), IC5.9 (3A), IC5.10 (3B), IC7.7 (GND), J1.3, J1.7, J1.12
unnamed: IC1.2 (A), IC5.6 (2Y)
unnamed: IC1.1 (B), IC5.3 (1Y)
unnamed: IC3.4 (Y), IC4.2 (1D)
unnamed: IC4.5 (1Q), IC4.12 (2D)
unnamed: IC5.11 (4Y), IC7.2 (1D)
unnamed: IC7.5 (1Q), IC7.12 (2D)
Slow Clock: IC5.4 (2A), IC7.3 (1CP), IC7.11 (2CP), J1.2
~Reset: IC4.1 (~1RD), IC4.13 (~2RD), IC7.1 (~1RD), IC7.13 (~2RD), J1.1
~Select Fast: IC3.2 (A), IC5.13 (4B), J1.9
